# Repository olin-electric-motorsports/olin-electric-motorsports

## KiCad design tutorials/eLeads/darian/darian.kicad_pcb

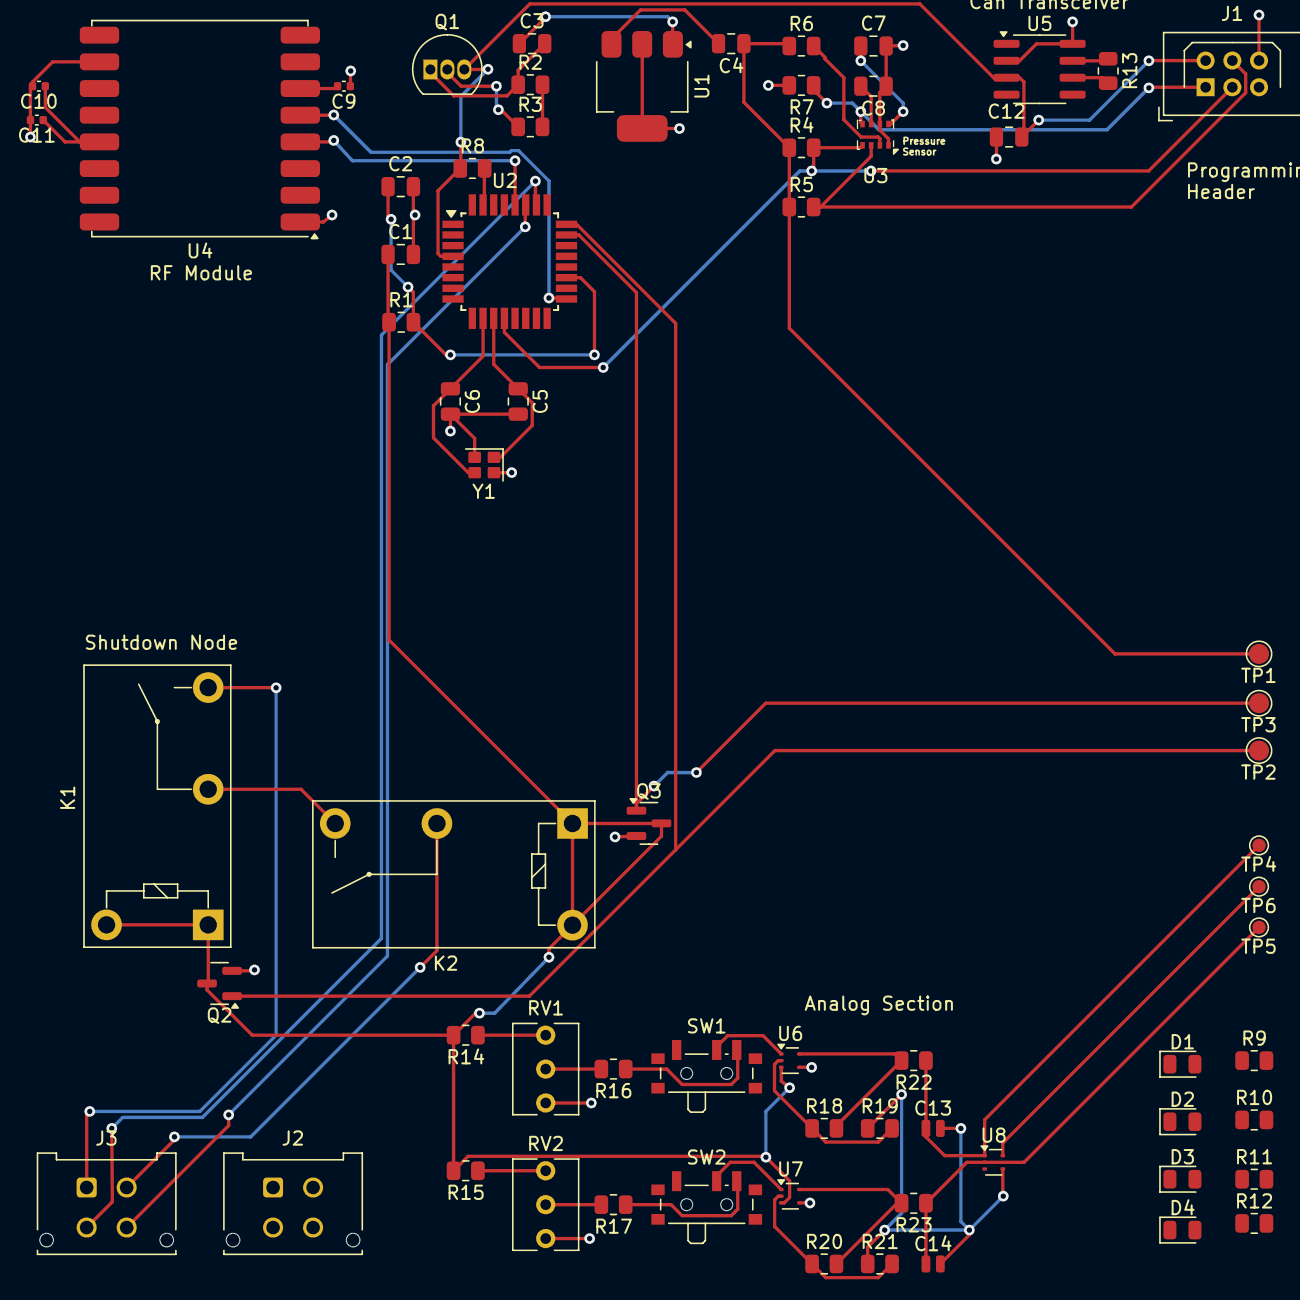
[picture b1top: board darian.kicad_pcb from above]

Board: 2 copper layers, 68 parts (0 on the bottom side), 51 nets.

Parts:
C1, C3, C4: C_1uF; C_0805_2012Metric
C2: C_100pF; C_0805_2012Metric
C5, C6: C_30pF; C_0805_2012Metric
C7, C8: C_100nF; C_0805_2012Metric
C9: C; C_0402_1005Metric
C10, C11: C_20pF; C_0402_1005Metric
C12: C_0.1uF; C_0805_2012Metric
C13, C14: C; C_0504_1310Metric
D1, D2, D3, D4: LED_0805; LED_0805_2012Metric
J1: CONN_02X03; Harwin_LTek-Male_2x03_P2.00mm_Vertical
J2, J3: MicroFit_RA_4; Molex_Micro-Fit_3.0_43045-0412_2x02_P3.00mm_Vertical
K1, K2: G5Q-1A4-DC5-5V; Relay_SPST_Omron-G5Q-1A
Q1: BC547; TO-92_Inline
Q2, Q3: SSM3K333R; SOT-23
R1: R_100; R_0805_2012Metric
R2, R3, R4, R5, R6, R7, R8: R_10K; R_0805_2012Metric
R9, R10, R11, R12, R14, R15, R16, R17, R18, R19, R20, R21, R22, R23: R_1K; R_0805_2012Metric
R13: R_120_DNP; R_0805_2012Metric
RV1, RV2: R_Potentiometer; Potentiometer_Vishay_T73XW_Horizontal
SW1, SW2: SW_SPDT; SW_SPDT_PCM12
TP1, TP2, TP3: TP; TestPoint_Pad_D1.5mm
TP4, TP5, TP6: TP_SMD; TestPoint_Pad_D1.0mm
U1: TC1262-33; SOT-223-3_TabPin2
U2: ATMEGA16M1; TQFP-32_7x7mm_P0.8mm
U3: BMP280; Bosch_LGA-8_2x2.5mm_P0.65mm_ClockwisePinNumbering
U4: RFM69HCW; HOPERF_RFM9XW_SMD
U5: TJA1042T; SOIC-8_3.9x4.9mm_P1.27mm
U6, U7, U8: ${SIM.PARAMS}; VSOF5
Y1: Crystal_12MHz; Crystal_SMD_SeikoEpson_FA128-4Pin_2.0x1.6mm

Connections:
+3.3V: C10.1, C11.1, R2.2, R3.2, U4.13 (3.3V)
+5V: C1.1, C12.2, J1.2, K1.1, K1.5, K2.1, K2.5, Q1.3 (E), Q2.3 (D), Q3.3 (D), R1.1, R8.1, R14.2, R15.2, U2.4 (VCC), U5.3 (VCC), U6.3 (V+), U7.3 (V+), U8.3 (V+)
/ANALOG_A: J3.3, U2.26 ((PCINT5/ADC6/INT2/ACMPN1/AMP2-)PB5)
/ANALOG_B: J3.4, U2.27 ((PCINT6/ADC7/PSCOUT1B)PB6)
/ANALOG_SS: Q2.1 (G), TP2.1 (TP), U2.24 ((PCINT4/AMP0+)PB4)
/Analog Section/ANALOG_OUT: TP6.1, U8.5
/CAN_RX: U2.7 ((PCINT11/T1/ICP1B/RXCAN)PC3), U5.4 (RXD)
/CAN_TX: U2.6 ((PCINT10/T0/TXCAN)PC2), U5.1 (TXD)
/MISO: J1.1, R7.1, U2.1 ((PCINT18/PSCIN2/OC1A/MISO_A)PD2), U2.8 ((PCINT0/MISO/PSCOUT2A)PB0), U3.5 (SDO), U4.2 (MISO)
/MOSI: J1.4, R5.2, U2.2 ((PCINT19/TXD/TXLIN/OC0A/~SS/MOSI_A)PD3), U2.9 ((PCINT1/MOSI/PSCOUT2B)PB1), U3.3 (SDI), U4.3 (MOSI)
/NSS: U2.17 ((PCINT12/ADC8/ACMPN3/AMP1-)PC4), U4.5 (NSS)
/Reset: R8.2, U2.31 ((PCINT24/OCD/~RESET)PE0)
/SCK: J1.3, R4.2, U2.12 ((PCINT20/ADC1/RXD/RXLIN/ICP1A/SCK_A)PD4), U2.28 ((PCINT7/ADC4/SCK/PSCOUT0B)PB7), U3.4 (SCK), U4.4 (SCK)
/SENSOR_SS: Q3.1 (G), TP3.1 (TP), U2.23 ((PCINT3/AMP0-)PB3)
/SHDN_IN: J3.1, K1.3
/SHDN_OUT: J3.2, K2.2
/Sensor: R6.2, U3.2 (CSB)
GND: C1.2, C2.2, C5.2, C6.2, C7.2, C8.1, C9.1, C10.2, C11.2, C12.1, C13.2, C14.2, J1.6, J2.2, Q2.2 (S), Q3.2 (S), R7.2, R9.1, R10.1, R11.1, R12.1, R19.1, R21.1, RV1.3, RV2.3, U1.2 (GND), U3.1 (GND), U3.7 (GND), U4.1 (GND), U4.10 (GND), U5.2 (GND), U5.8 (STB), U6.4 (V-), U7.4 (V-), U8.4 (V-), Y1.2, Y1.4
GND1: U2.5 (GND), U2.20 (AGND)
unnamed: D1.2 (A), R9.2
unnamed: D2.2 (A), R10.2
unnamed: D3.2 (A), R11.2
unnamed: D4.2 (A), R12.2
unnamed: K1.2, K2.3
unnamed: Q1.2 (B), R3.1
unnamed: C3.2, Q1.1 (C), R2.1
unnamed: R14.1, RV1.1
unnamed: R15.1, RV2.1
unnamed: R16.2, RV1.2
unnamed: R17.2, RV2.2
unnamed: R18.2, R22.2, U6.5
unnamed: R20.2, R23.2, U7.5
unnamed: SW1.2 (B), U6.1 (+)
unnamed: R16.1, SW1.3 (C)
unnamed: SW2.2 (B), U7.1 (+)
unnamed: R17.1, SW2.3 (C)
unnamed: C4.1, R4.1, R5.1, R6.1, TP1.1 (TP)
unnamed: C3.1, U1.1 (VI)
unnamed: C4.2, U1.3 (VO)
unnamed: C6.1, U2.10 ((PCINT25/OC0B/XTAL1)PE1), Y1.3
unnamed: C5.1, U2.11 ((PCINT26/ADC0/XTAL2)PE2), Y1.1
unnamed: C2.1, R1.2, U2.19 (AVCC)
unnamed: C7.1, U3.8 (VDD)
unnamed: C8.2, U3.6 (VDDIO)
unnamed: C9.2, U4.6 (RESET)
unnamed: R13.1, U5.7 (CANH)
unnamed: R13.2, U5.6 (CANL)
unnamed: R18.1, R19.2, U6.2 (-)
unnamed: R20.1, R21.2, U7.2 (-)
unnamed: C13.1, R22.1, TP4.1, U8.1 (+)
unnamed: C14.1, R23.1, TP5.1, U8.2 (-)

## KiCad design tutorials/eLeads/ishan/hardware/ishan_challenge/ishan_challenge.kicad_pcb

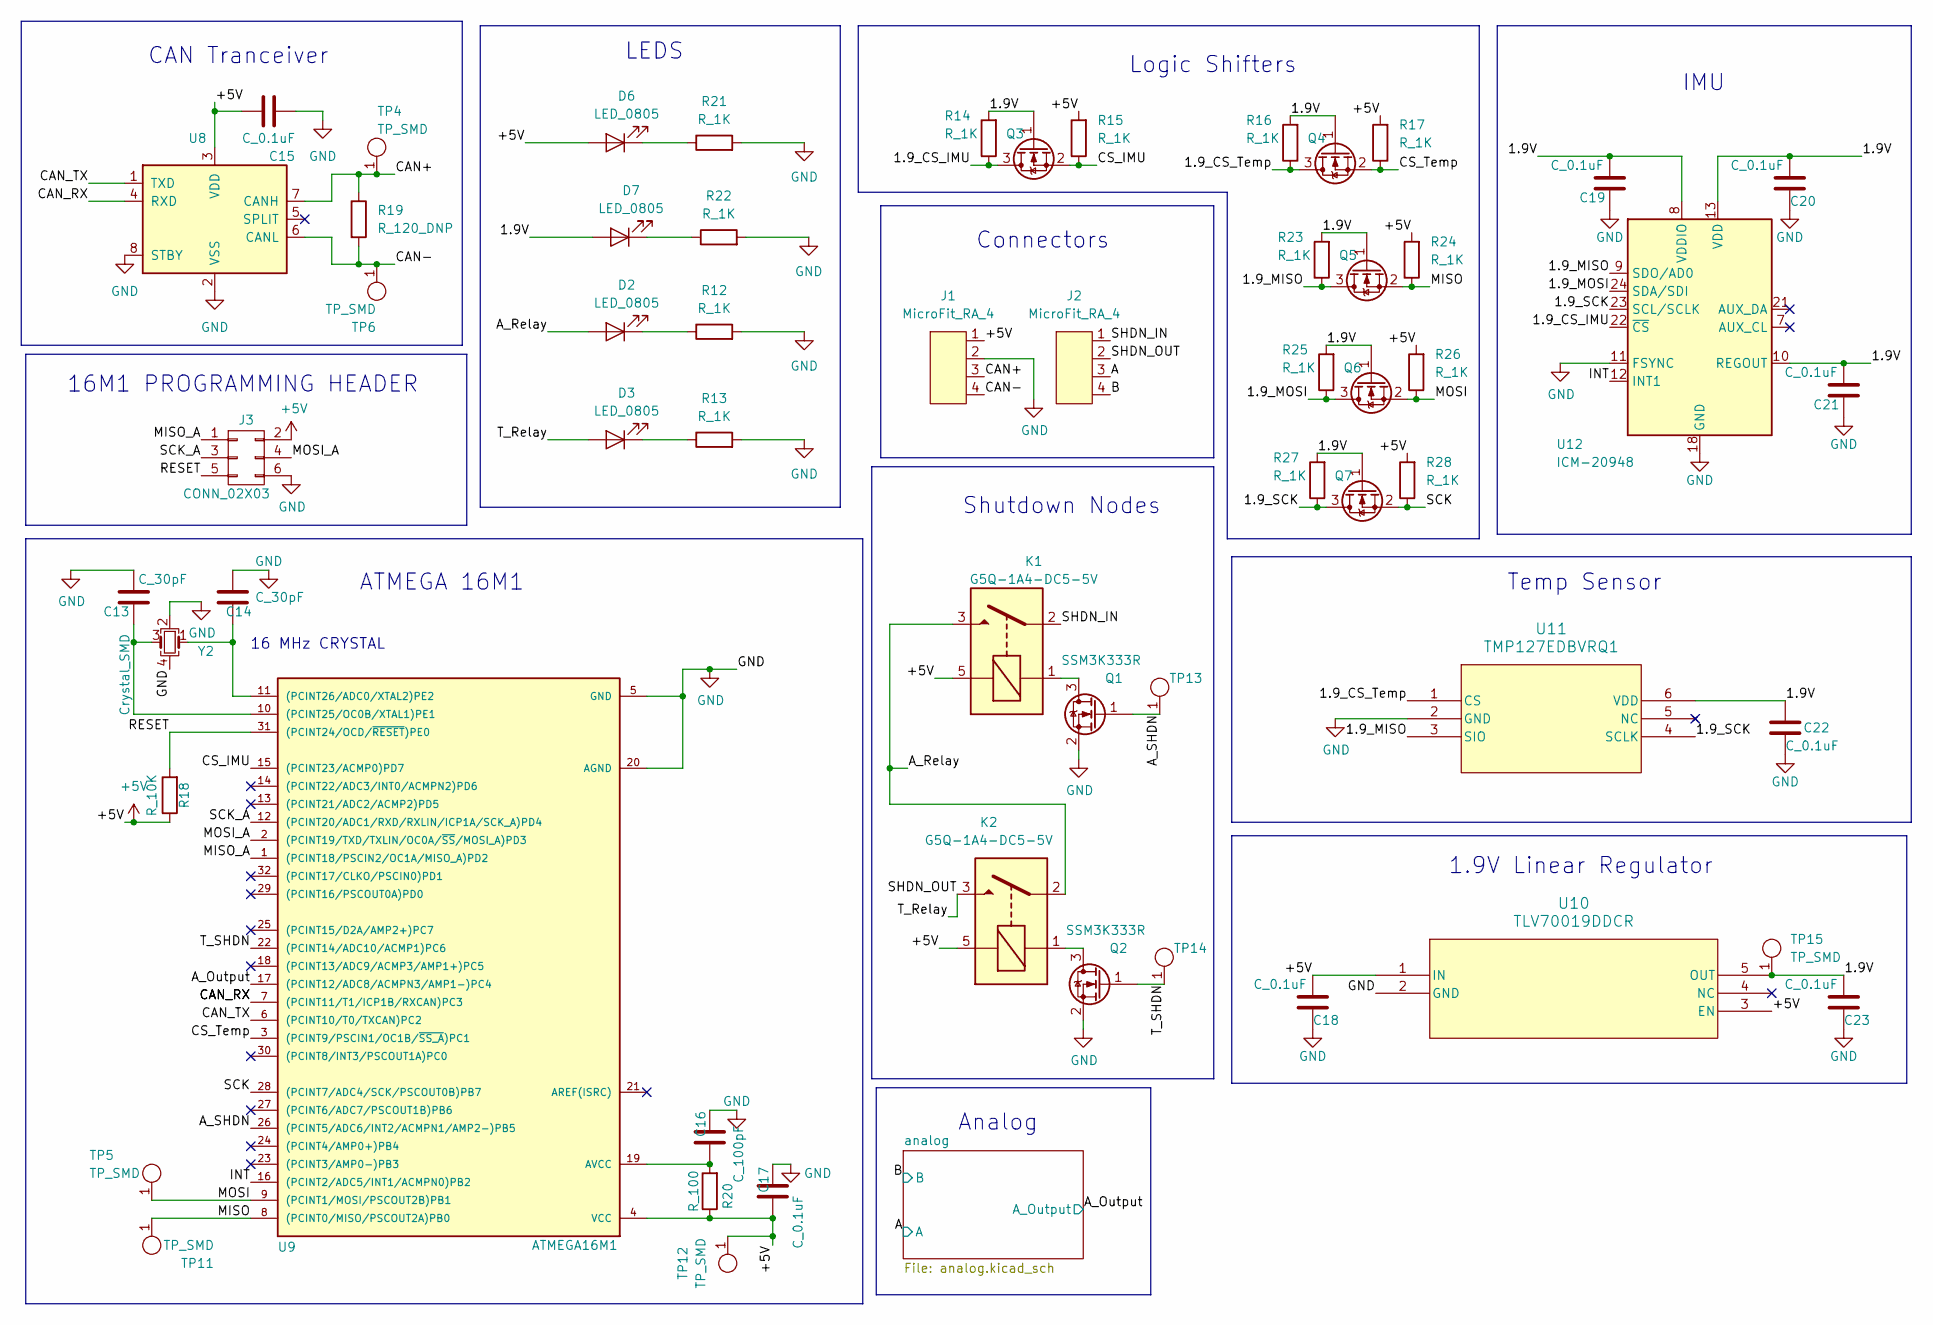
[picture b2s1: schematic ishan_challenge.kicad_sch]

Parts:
C13, C14: C_30pF; C_0603; MPN 1276-1130-1-ND
C15, C17: C_0.1uF; C_0603; MPN 478-3352-1-ND
C16: C_100pF; C_0603; MPN 732-7852-1-ND
C18, C19, C20, C21, C22, C23: C_0.1uF; C_0603; MPN 1276-1130-1-ND
D2, D3, D6, D7: LED_0805; LED_0805_OEM; MPN 475-1410-1-ND
J1, J2: MicroFit_RA_4
J3: CONN_02X03; Pin_Header_Straight_2x03; MPN 609-3234-ND
K1, K2: G5Q-1A4-DC5-5V; Relay_SPST_OMRON-G5Q-1A4_OEM; MPN Z3632-ND
Q1, Q2, Q3, Q4, Q5, Q6, Q7: SSM3K333R; SOT-23F; MPN SSM3K333RLFCT-ND
R12, R13, R14, R15, R16, R17, R21, R22, R23, R24, R25, R26, R27, R28: R_1K; R_0603; MPN RNCP0805FTD1K00CT-ND
R18: R_10K; R_0603; MPN CRS0805-FX-1002ELFCT-ND
R19: R_120_DNP; R_0603; MPN 667-ERJ-6ENF1200V
R20: R_100; R_0603; MPN RNCP0805FTD100RCT-ND
TP4, TP5, TP6, TP11, TP12, TP13, TP14, TP15: TP_SMD; Test_Point_SMD; MPN 5019
U8: MCP2561-E_SN; SOIC-8_3.9x4.9mm_Pitch1.27mm_OEM; MPN MCP2561-E/SN-ND
U9: ATMEGA16M1; TQFP-32_7x7mm_Pitch0.8mm; MPN ATMEGA16M1-AU-ND
U10: TLV70019DDCR
U11: TMP127EDBVRQ1
U12: ICM-20948; InvenSense_QFN-24_3x3mm_P0.4mm
Y2: Crystal_SMD; Crystal_SMD_FA238; MPN 887-1125-1-ND

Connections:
+5V: C15.1, C17.1, C18.2, D6.2 (A), J1.1, J3.2, K1.5, K2.5, R15.2, R17.2, R18.1, R20.1, R24.2, R26.2, R28.2, TP12.1, U8.3 (VDD), U9.4 (VCC), U10.1 (IN), U10.3 (EN); also elsewhere on the board
/1.9V: C19.2, C20.2, C21.2, C22.2, C23.2, D7.2 (A), Q3.1 (G), Q4.1 (G), Q5.1 (G), Q6.1 (G), Q7.1 (G), R14.2, R16.2, R23.2, R25.2, R27.2, TP15.1, U10.5 (OUT), U11.6 (VDD), U12.8 (VDDIO), U12.10 (REGOUT), U12.13 (VDD)
/1.9_CS_IMU: Q3.3 (D), R14.1, U12.22 (~CS)
/1.9_CS_Temp: Q4.3 (D), R16.1, U11.1 (CS)
/1.9_MISO: Q5.3 (D), R23.1, U11.3 (SIO), U12.9 (SDO/AD0)
/1.9_MOSI: Q6.3 (D), R25.1, U12.24 (SDA/SDI)
/1.9_SCK: Q7.3 (D), R27.1, U11.4 (SCLK), U12.23 (SCL/SCLK)
/A: J2.3; also elsewhere on the board
/A_Output: U9.17 ((PCINT12/ADC8/ACMPN3/AMP1-)PC4); also elsewhere on the board
/A_Relay: D2.2 (A), K1.3, K2.2
/A_SHDN: Q1.1 (G), TP13.1, U9.26 ((PCINT5/ADC6/INT2/ACMPN1/AMP2-)PB5)
/B: J2.4; also elsewhere on the board
/CAN+: J1.3, R19.1, TP4.1, U8.7 (CANH)
/CAN-: J1.4, R19.2, TP6.1, U8.6 (CANL)
/CAN_RX: U8.4 (RXD), U9.7 ((PCINT11/T1/ICP1B/RXCAN)PC3)
/CAN_TX: U8.1 (TXD), U9.6 ((PCINT10/T0/TXCAN)PC2)
/CS_IMU: Q3.2 (S), R15.1, U9.15 ((PCINT23/ACMP0)PD7)
/CS_Temp: Q4.2 (S), R17.1, U9.3 ((PCINT9/PSCIN1/OC1B/~SS_A)PC1)
/INT: U9.16 ((PCINT2/ADC5/INT1/ACMPN0)PB2), U12.12 (INT1)
/MISO: Q5.2 (S), R24.1, TP11.1, U9.8 ((PCINT0/MISO/PSCOUT2A)PB0)
/MISO_A: J3.1, U9.1 ((PCINT18/PSCIN2/OC1A/MISO_A)PD2)
/MOSI: Q6.2 (S), R26.1, TP5.1, U9.9 ((PCINT1/MOSI/PSCOUT2B)PB1)
/MOSI_A: J3.4, U9.2 ((PCINT19/TXD/TXLIN/OC0A/~SS/MOSI_A)PD3)
/RESET: J3.5, R18.2, U9.31 ((PCINT24/OCD/~RESET)PE0)
/SCK: Q7.2 (S), R28.1, U9.28 ((PCINT7/ADC4/SCK/PSCOUT0B)PB7)
/SCK_A: J3.3, U9.12 ((PCINT20/ADC1/RXD/RXLIN/ICP1A/SCK_A)PD4)
/SHDN_IN: J2.1, K1.2
/SHDN_OUT: D3.2 (A), J2.2, K2.3
/T_SHDN: Q2.1 (G), TP14.1, U9.22 ((PCINT14/ADC10/ACMP1)PC6)
unnamed: D2.1 (K), R12.1
unnamed: D3.1 (K), R13.1
unnamed: D6.1 (K), R21.1
unnamed: D7.1 (K), R22.1
unnamed: K1.1, Q1.3 (D)
unnamed: K2.1, Q2.3 (D)
unnamed: C13.1, U9.10 ((PCINT25/OC0B/XTAL1)PE1), Y2.3
unnamed: C14.1, U9.11 ((PCINT26/ADC0/XTAL2)PE2), Y2.1
unnamed: C16.1, R20.2, U9.19 (AVCC)

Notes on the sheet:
Logic Shifters
LEDS
Connectors
Analog
Shutdown Nodes
Temp Sensor
IMU
16M1 PROGRAMMING HEADER
16 MHz CRYSTAL
1.9V Linear Regulator
CAN Tranceiver
ATMEGA 16M1

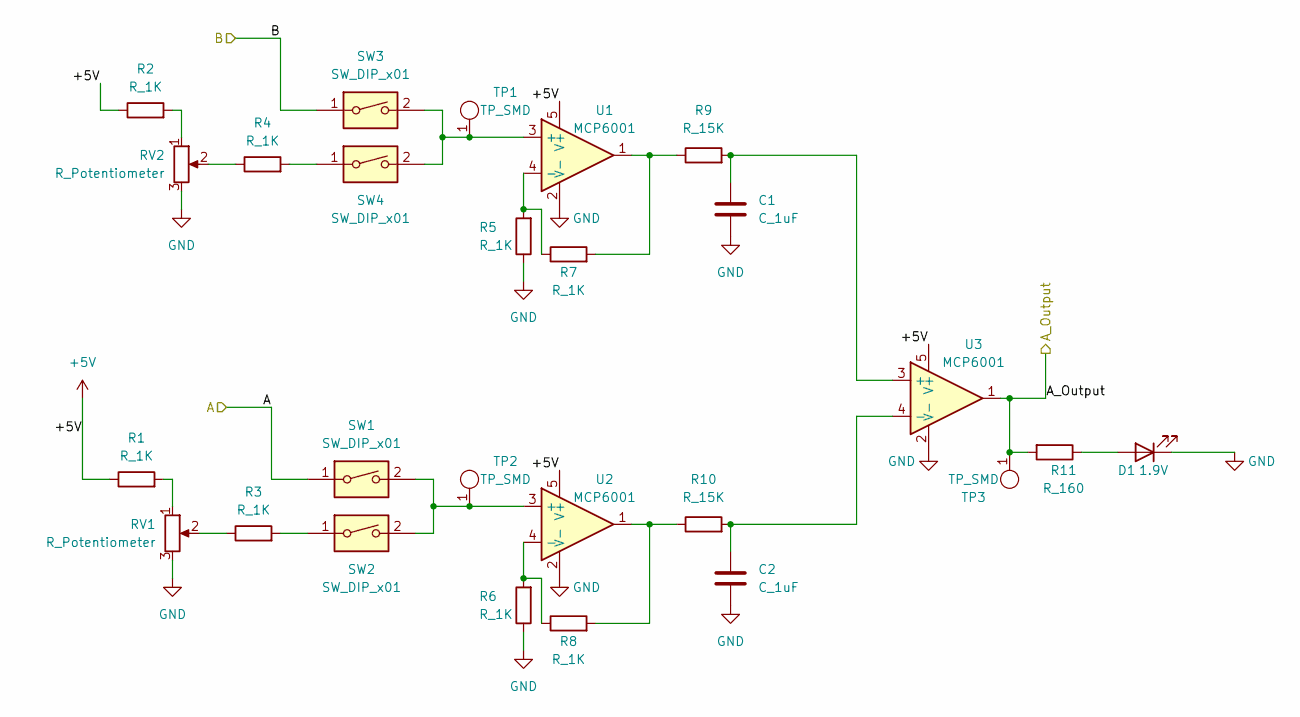
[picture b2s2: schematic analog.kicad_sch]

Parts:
C1, C2: C_1uF; C_0603; MPN 1276-6470-1-ND
D1: 1.9V; LED_0805_OEM; MPN B1701TW--20P000314U1930
R1, R2, R3, R4, R5, R6, R7, R8: R_1K; R_0603; MPN RNCP0805FTD1K00CT-ND
R9, R10: R_15K; R_0603; MPN RNCP0805FTD1K00CT-ND
R11: R_160; R_0603; MPN 311-4.7KARCT-ND
RV1, RV2: R_Potentiometer; Potentiometer_Trimmer_Bourns_TCC3
SW1, SW2, SW3, SW4: SW_DIP_x01; SW_DIP_SPSTx01_Slide_9.78x4.72mm_W8.61mm_P2.54mm
TP1, TP2, TP3: TP_SMD; Test_Point_SMD; MPN 5019
U1, U2, U3: MCP6001; SOT-23-5_OEM; MPN MCP6001T-I/OTCT-ND

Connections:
+5V: R1.1, R2.1, U1.5 (V+), U2.5 (V+), U3.5 (V+); also elsewhere on the board
/A: SW1.1; also elsewhere on the board
/A_Output: R11.2, TP3.1, U3.1; also elsewhere on the board
/B: SW3.1; also elsewhere on the board
unnamed: D1.2 (A), R11.1
unnamed: R1.2, RV1.1
unnamed: R2.2, RV2.1
unnamed: R3.1, RV1.2
unnamed: R3.2, SW2.1
unnamed: R4.1, RV2.2
unnamed: R4.2, SW4.1
unnamed: R7.2, R9.1, U1.1
unnamed: R8.2, R10.1, U2.1
unnamed: SW3.2, SW4.2, TP1.1, U1.3 (+)
unnamed: R5.2, R7.1, U1.4 (-)
unnamed: SW1.2, SW2.2, TP2.1, U2.3 (+)
unnamed: R6.2, R8.1, U2.4 (-)
unnamed: C1.1, R9.2, U3.3 (+)
unnamed: C2.1, R10.2, U3.4 (-)

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
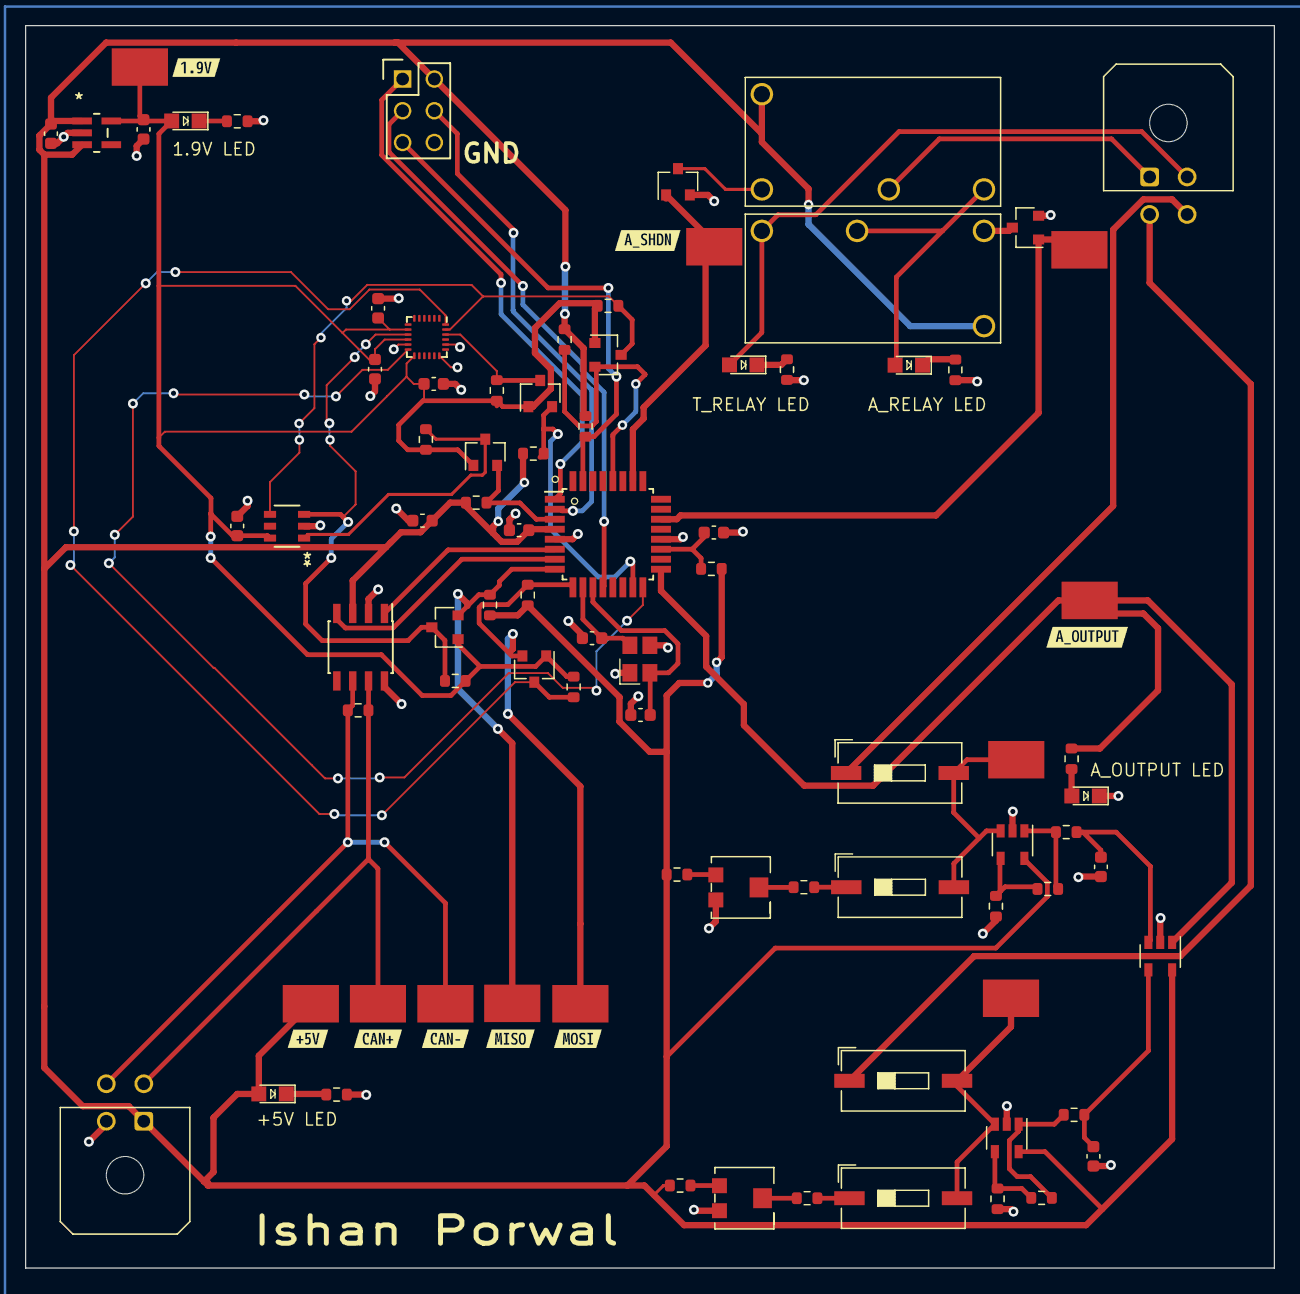
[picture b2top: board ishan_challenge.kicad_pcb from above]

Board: 2 copper layers, 99.9 x 99.4 mm, 92 parts (0 on the bottom side), 54 nets.

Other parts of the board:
kibuzzard-66BA7B45: G***; kibuzzard-66BA7B45
kibuzzard-66BA78DD: G***; kibuzzard-66BA78DD
kibuzzard-66BA78FC: G***; kibuzzard-66BA78FC
kibuzzard-66BA794C: G***; kibuzzard-66BA794C
kibuzzard-66BA7730: G***; kibuzzard-66BA7730
kibuzzard-66BA7778: G***; kibuzzard-66BA7778
kibuzzard-66BA7799: G***; kibuzzard-66BA7799
kibuzzard-66BA7937: G***; kibuzzard-66BA7937

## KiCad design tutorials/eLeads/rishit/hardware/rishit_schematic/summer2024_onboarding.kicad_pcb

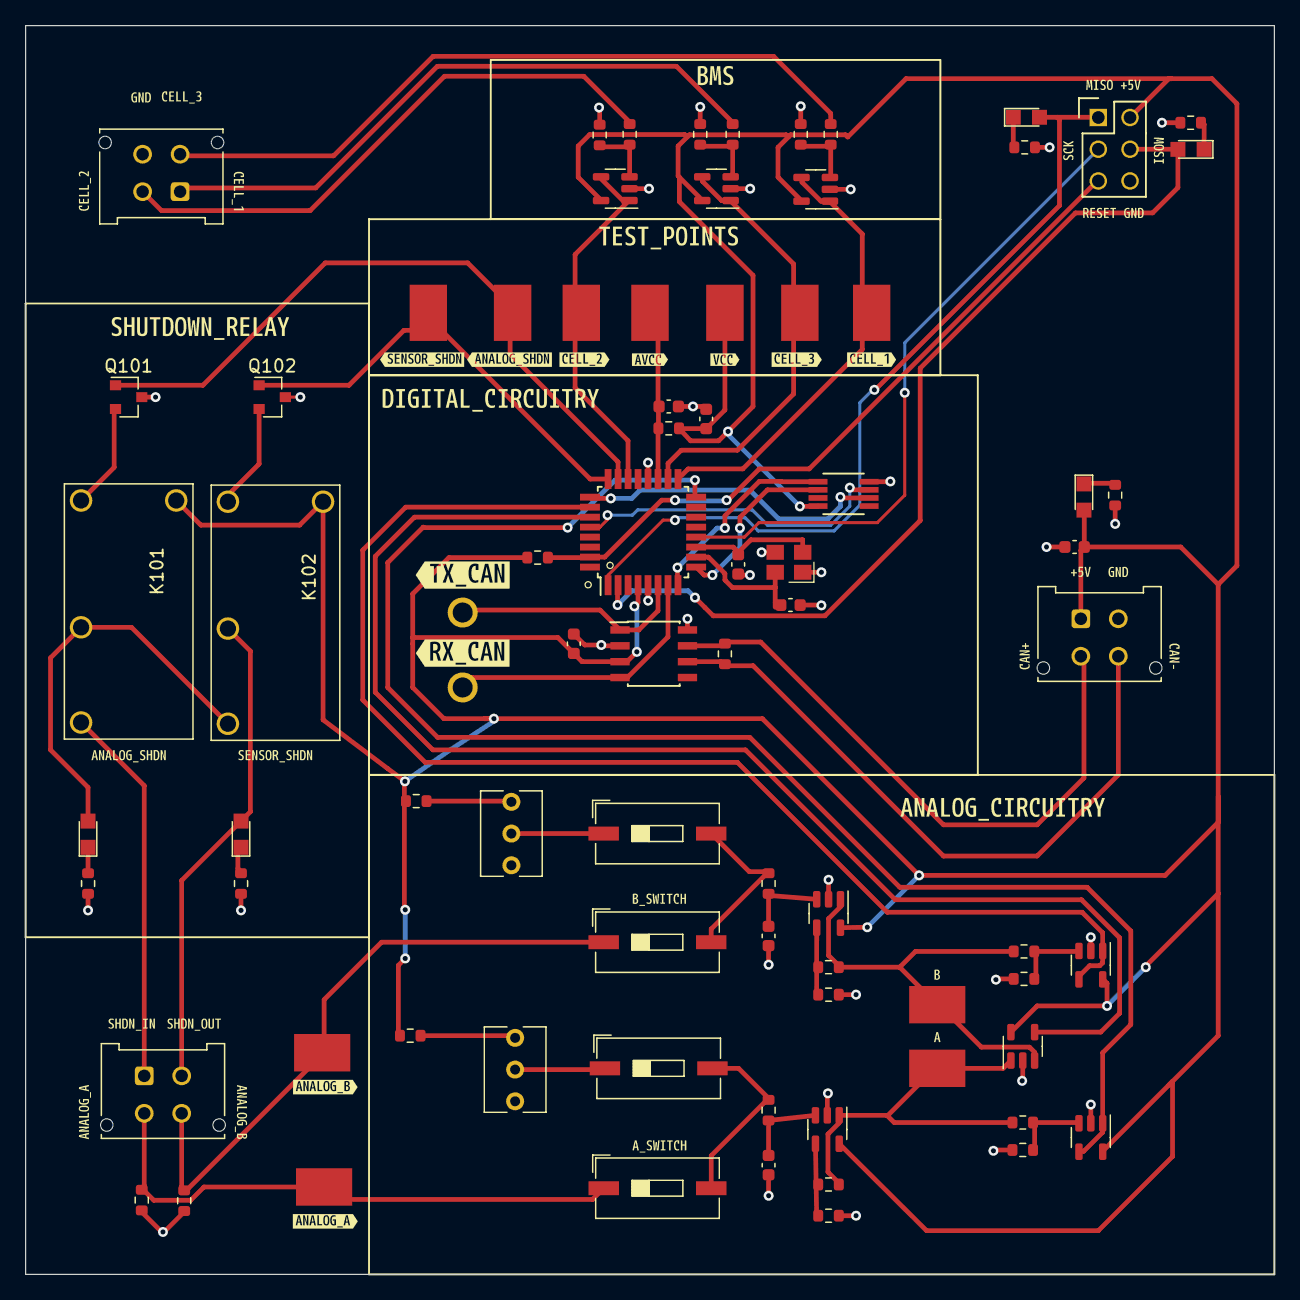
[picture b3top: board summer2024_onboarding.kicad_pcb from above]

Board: 2 copper layers, 100.0 x 100.0 mm, 120 parts (0 on the bottom side), 57 nets.

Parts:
C101, C105, C108: C_0.1uF; C_0603
C102: C_100pF; C_0603
C103, C104: C_30pF; C_0603
C106, C107: C_10uF; C_0603
D101, D104, D105: 5V_LED; CHIPLED_0805
D102: MISO_PROG_LED; CHIPLED_0805
D103: MOSI_PROG_LED; CHIPLED_0805
J101: Conn_02x03_Odd_Even; Pin_Header_Straight_2x03
J102, J103, J104: MicroFit_VT_4
K101, K102: G5Q-1A4-DC5-5V; Relay_SPST_OMRON-G5Q-1A4_OEM
Q101, Q102: SSM3K333R; SOT-23F
R101: R_100; R_0603
R102: R_10K; R_0603
R103: R_120_DNP; R_0603
R104, R105, R106, R107, R108, R109, R110, R111, R112, R113, R114, R115, R116, R117, R118, R119, R120, R121, R122, R123, R124, R127, R128: R_1K; R_0603
R125, R126: R_100K; R_0603
RV101, RV102: R_Potentiometer; Potentiometer_Vishay_T73XW_Horizontal
SW101, SW102, SW103, SW104: SW_DIP_x01; SW_DIP_SPSTx01_Slide_9.78x4.72mm_W8.61mm_P2.54mm
TP101, TP102, TP104, TP107, TP108, TP109, TP110, TP111, TP112, TP113, TP115: TP_SMD; Test_Point_SMD
TP105, TP106: TP; tp_1.6mm
U101: ATMEGA16M1; TQFP-32_7x7mm_Pitch0.8mm
U102: MCP2561-E_SN; SOIC-8_3.9x4.9mm_Pitch1.27mm_OEM
U103: TC72-3.3MUATR; MSOP8_MC_MCH
U104, U105, U106, U107, U109, U110, U111: MCP6001; SOT-23-5
U108: LM397; SOT-23-5
Y101: Crystal_16MHz_18pF; Crystal_SMD_FA238
kibuzzard-66BE6AB2: G***; kibuzzard-66BE6AB2
kibuzzard-66BE6ACE: G***; kibuzzard-66BE6ACE
kibuzzard-66BE71B0: G***; kibuzzard-66BE71B0
kibuzzard-66BE71DF: G***; kibuzzard-66BE71DF
kibuzzard-66BE71E9: G***; kibuzzard-66BE71E9
kibuzzard-66BE71F1: G***; kibuzzard-66BE71F1
kibuzzard-66BE71FF: G***; kibuzzard-66BE71FF
kibuzzard-66BE72A1: G***; kibuzzard-66BE72A1
kibuzzard-66BE72AD: G***; kibuzzard-66BE72AD
kibuzzard-66BE72B5: G***; kibuzzard-66BE72B5
kibuzzard-66BE72C2: G***; kibuzzard-66BE72C2
kibuzzard-66BE72DA: G***; kibuzzard-66BE72DA
kibuzzard-66BE72F1: G***; kibuzzard-66BE72F1
kibuzzard-66BE686E: G***; kibuzzard-66BE686E
kibuzzard-66BE690E: G***; kibuzzard-66BE690E
kibuzzard-66BE691A: G***; kibuzzard-66BE691A
kibuzzard-66BE692C: G***; kibuzzard-66BE692C
kibuzzard-66BE702D: G***; kibuzzard-66BE702D
kibuzzard-66BE725D: G***; kibuzzard-66BE725D
kibuzzard-66BE726A: G***; kibuzzard-66BE726A
kibuzzard-66BE736C: G***; kibuzzard-66BE736C
kibuzzard-66BE6860: G***; kibuzzard-66BE6860
kibuzzard-66BE6937: G***; kibuzzard-66BE6937
kibuzzard-66BE7023: G***; kibuzzard-66BE7023
kibuzzard-66BE7118: G***; kibuzzard-66BE7118
kibuzzard-66BE7123: G***; kibuzzard-66BE7123
kibuzzard-66BE7184: G***; kibuzzard-66BE7184
kibuzzard-66BE7235: G***; kibuzzard-66BE7235
kibuzzard-66BE7274: G***; kibuzzard-66BE7274
kibuzzard-66BF40E2: G***; kibuzzard-66BF40E2
kibuzzard-66BF42D8: G***; kibuzzard-66BF42D8
kibuzzard-66BF42E1: G***; kibuzzard-66BF42E1
kibuzzard-66BF415D: G***; kibuzzard-66BF415D
kibuzzard-66BF4127: G***; kibuzzard-66BF4127
kibuzzard-66BF4146: G***; kibuzzard-66BF4146
kibuzzard-66BF4157: G***; kibuzzard-66BF4157
kibuzzard-66BF4165: G***; kibuzzard-66BF4165
kibuzzard-66BF4194: G***; kibuzzard-66BF4194
kibuzzard-66BF4328: G***; kibuzzard-66BF4328
kibuzzard-66BF4330: G***; kibuzzard-66BF4330

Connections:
+5V: C101.1, C105.1, C108.2, D101.2 (A), J101.2, J102.1, K101.5, K102.5, R101.1, R102.2, R107.1, R108.1, TP102.1, U101.4 (VCC), U102.3 (VDD), U103.8, U104.5 (V+), U105.5 (V+), U106.5 (V+), U107.5 (V+), U108.5 (V+), U109.5 (V+), U110.5 (V+), U111.5 (V+)
/ANALOG_A: J103.3, R126.1, SW103.1, TP115.1
/ANALOG_B: J103.4, R125.1, SW101.1, TP108.1
/ANALOG_OUT: U101.27 ((PCINT6/ADC7/PSCOUT1B)PB6), U108.4
/ANALOG_SHDN: Q101.1 (G), TP104.1, U101.23 ((PCINT3/AMP0-)PB3)
/ANALOG_VOLTAGE_A: U101.16 ((PCINT2/ADC5/INT1/ACMPN0)PB2), U106.1, U106.4 (-)
/ANALOG_VOLTAGE_B: U101.26 ((PCINT5/ADC6/INT2/ACMPN1/AMP2-)PB5), U107.1, U107.4 (-)
/CAN+: J102.3, R103.1, U102.7 (CANH)
/CAN-: J102.4, R103.2, U102.6 (CANL)
/CE: U101.25 ((PCINT15/D2A/AMP2+)PC7), U103.2
/CELL_1: J104.1, R119.1
/CELL_2: J104.2, R123.1
/CELL_3: J104.3, R120.1
/MISO: U101.8 ((PCINT0/MISO/PSCOUT2A)PB0), U103.5
/MISO_A: D102.2 (A), J101.1, U101.1 ((PCINT18/PSCIN2/OC1A/MISO_A)PD2)
/MOSI: U101.9 ((PCINT1/MOSI/PSCOUT2B)PB1), U103.6
/MOSI_A: D103.2 (A), J101.4, U101.2 ((PCINT19/TXD/TXLIN/OC0A/~SS/MOSI_A)PD3)
/RESET: J101.5, R102.1, U101.31 ((PCINT24/OCD/~RESET)PE0)
/RXCAN: TP106.1 (TP), U101.7 ((PCINT11/T1/ICP1B/RXCAN)PC3), U102.4 (RXD)
/SCK: U101.28 ((PCINT7/ADC4/SCK/PSCOUT0B)PB7), U103.3
/SCK_A: J101.3, U101.12 ((PCINT20/ADC1/RXD/RXLIN/ICP1A/SCK_A)PD4)
/SENSOR_SHDN: Q102.1 (G), TP107.1, U101.24 ((PCINT4/AMP0+)PB4)
/TXCAN: TP105.1 (TP), U101.6 ((PCINT10/T0/TXCAN)PC2), U102.1 (TXD)
/VOLTAGE_CELL_1: TP110.1, U101.17 ((PCINT12/ADC8/ACMPN3/AMP1-)PC4), U110.1, U110.4 (-)
/VOLTAGE_CELL_2: TP112.1, U101.22 ((PCINT14/ADC10/ACMP1)PC6), U111.1, U111.4 (-)
/VOLTAGE_CELL_3: TP111.1, U101.18 ((PCINT13/ADC9/ACMP3/AMP1+)PC5), U109.1, U109.4 (-)
GND: C101.2, C102.2, C103.2, C104.2, C105.2, C106.2, C107.2, C108.1, J101.6, J102.2, J104.4, Q101.3 (D), Q102.3 (D), R104.2, R105.2, R106.2, R112.2, R114.2, R117.2, R118.2, R121.2, R122.2, R124.2, R125.2, R126.2, R127.2, R128.2, RV101.3, RV102.3, U101.5 (GND), U101.20 (AGND), U102.2 (VSS), U102.8 (STBY), U103.4, U104.2 (V-), U105.2 (V-), U106.2 (V-), U107.2 (V-), U108.2 (V-), U109.2 (V-), U110.2 (V-), U111.2 (V-), Y101.2, Y101.4
unnamed: D101.1 (K), R104.1
unnamed: D102.1 (K), R105.1
unnamed: D103.1 (K), R106.1
unnamed: D104.2 (A), K101.2, K102.3
unnamed: D104.1 (K), R127.1
unnamed: D105.1 (K), R128.1
unnamed: K101.1, Q101.2 (S)
unnamed: K102.1, Q102.2 (S)
unnamed: R107.2, RV101.1
unnamed: R108.2, RV102.1
unnamed: R109.1, SW101.2, SW102.2
unnamed: R110.1, SW103.2, SW104.2
unnamed: RV101.2, SW104.1
unnamed: RV102.2, SW102.1
unnamed: C104.1, U101.10 ((PCINT25/OC0B/XTAL1)PE1), Y101.3
unnamed: C103.1, U101.11 ((PCINT26/ADC0/XTAL2)PE2), Y101.1
unnamed: C102.1, R101.2, TP101.1, U101.19 (AVCC)
unnamed: C106.1, R109.2, U104.3 (+)
unnamed: R111.2, R112.1, U104.4 (-)
unnamed: C107.1, R110.2, U105.3 (+)
unnamed: R113.2, R114.1, U105.4 (-)
unnamed: R115.2, R117.1, U106.3 (+)
unnamed: R116.2, R118.1, U107.3 (+)
unnamed: R111.1, R116.1, TP109.1, U104.1, U108.3 (+)
unnamed: R113.1, R115.1, TP113.1, U105.1, U108.1 (-)
unnamed: R119.2, R121.1, U109.3 (+)
unnamed: R120.2, R122.1, U110.3 (+)
unnamed: R123.2, R124.1, U111.3 (+)
SHDN_IN: J103.1, K101.3
SHDN_OUT: D105.2 (A), J103.2, K102.2

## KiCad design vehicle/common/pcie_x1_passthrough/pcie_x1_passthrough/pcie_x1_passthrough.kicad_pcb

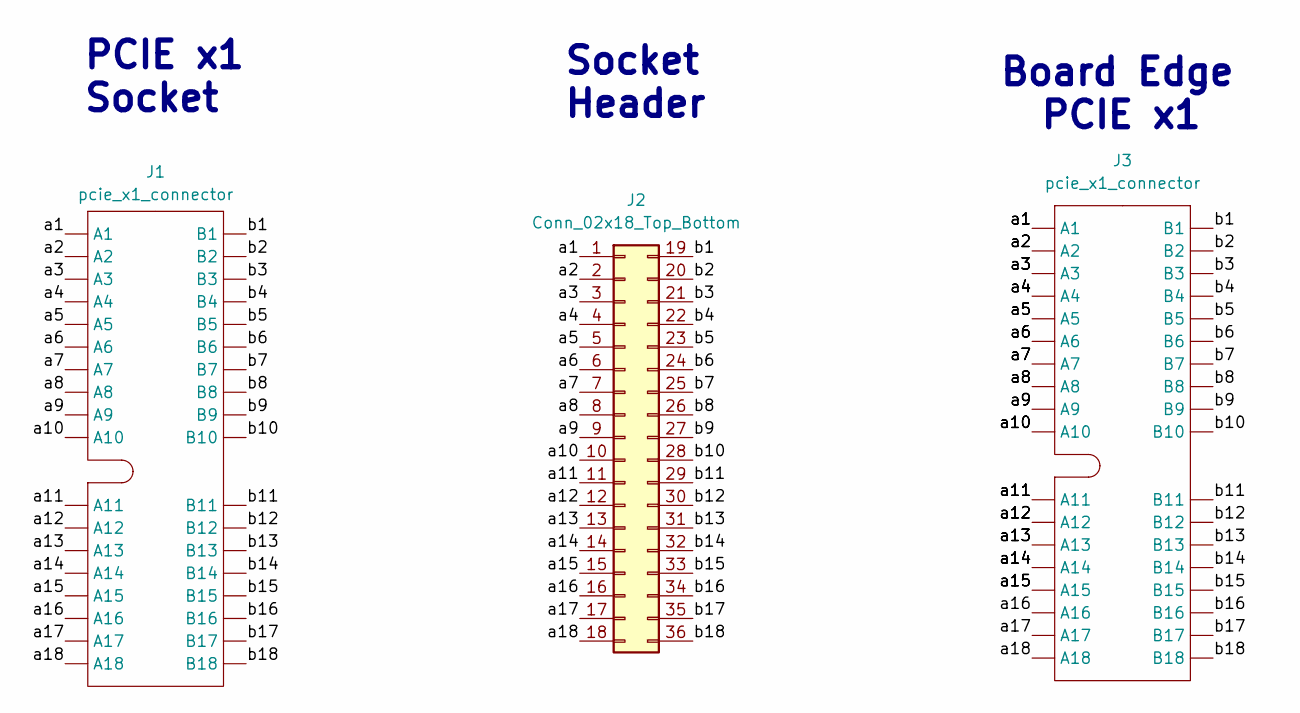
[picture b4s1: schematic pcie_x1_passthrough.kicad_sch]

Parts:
J1: pcie_x1_connector; pcie_x1_socket
J2: Conn_02x18_Top_Bottom; PinSocket_2x18_P2.54mm_Vertical
J3: pcie_x1_connector; BUS_PCIexpress_x1

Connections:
/a1: J1.A1, J2.1, J3.A1
/a2: J1.A2, J2.2, J3.A2
/a3: J1.A3, J2.3, J3.A3
/a4: J1.A4, J2.4, J3.A4
/a5: J1.A5, J2.5, J3.A5
/a6: J1.A6, J2.6, J3.A6
/a7: J1.A7, J2.7, J3.A7
/a8: J1.A8, J2.8, J3.A8
/a9: J1.A9, J2.9, J3.A9
/a10: J1.A10, J2.10, J3.A10
/a11: J1.A11, J2.11, J3.A11
/a12: J1.A12, J2.12, J3.A12
/a13: J1.A13, J2.13, J3.A13
/a14: J1.A14, J2.14, J3.A14
/a15: J1.A15, J2.15, J3.A15
/a16: J1.A16, J2.16, J3.A16
/a17: J1.A17, J2.17, J3.A17
/a18: J1.A18, J2.18, J3.A18
/b1: J1.B1, J2.19, J3.B1
/b2: J1.B2, J2.20, J3.B2
/b3: J1.B3, J2.21, J3.B3
/b4: J1.B4, J2.22, J3.B4
/b5: J1.B5, J2.23, J3.B5
/b6: J1.B6, J2.24, J3.B6
/b7: J1.B7, J2.25, J3.B7
/b8: J1.B8, J2.26, J3.B8
/b9: J1.B9, J2.27, J3.B9
/b10: J1.B10, J2.28, J3.B10
/b11: J1.B11, J2.29, J3.B11
/b12: J1.B12, J2.30, J3.B12
/b13: J1.B13, J2.31, J3.B13
/b14: J1.B14, J2.32, J3.B14
/b15: J1.B15, J2.33, J3.B15
/b16: J1.B16, J2.34, J3.B16
/b17: J1.B17, J2.35, J3.B17
/b18: J1.B18, J2.36, J3.B18

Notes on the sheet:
Socket Header
Board Edge PCIE x1
PCIE x1 Socket

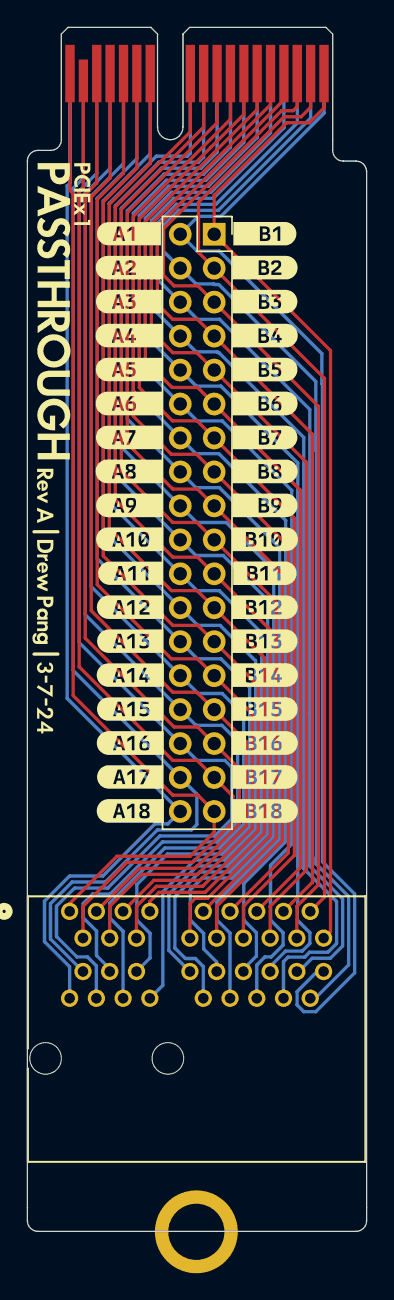
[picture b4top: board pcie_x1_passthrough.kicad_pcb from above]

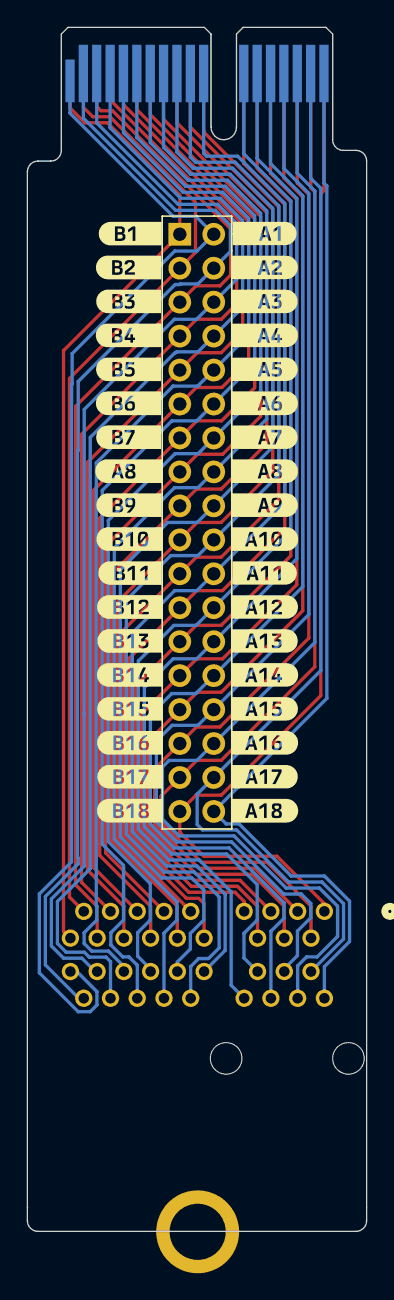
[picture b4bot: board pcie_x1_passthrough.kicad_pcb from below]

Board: 2 copper layers, 25.4 x 90.1 mm, 79 parts (37 on the bottom side), 36 nets.

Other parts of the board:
J2#2: Conn_02x18_Top_Bottom; PinSocket_2x18_P2.54mm_Vertical
kibuzzard-65E95D19: G***; kibuzzard-65E95D19
kibuzzard-65E95DA8: G***; kibuzzard-65E95DA8
kibuzzard-65E95DDF, kibuzzard-65E95DDF#2: G***; kibuzzard-65E95DDF
kibuzzard-65E95DE4: G***; kibuzzard-65E95DE4
kibuzzard-65E95DEB: G***; kibuzzard-65E95DEB
kibuzzard-65E95DEF: G***; kibuzzard-65E95DEF
kibuzzard-65E95DF3: G***; kibuzzard-65E95DF3
kibuzzard-65E95DF8: G***; kibuzzard-65E95DF8
kibuzzard-65E95DFB: G***; kibuzzard-65E95DFB
kibuzzard-65E95E04: G***; kibuzzard-65E95E04
kibuzzard-65E95E8F: G***; kibuzzard-65E95E8F
kibuzzard-65E95E9B: G***; kibuzzard-65E95E9B
kibuzzard-65E95E9E: G***; kibuzzard-65E95E9E
kibuzzard-65E95E93: G***; kibuzzard-65E95E93
kibuzzard-65E95E97: G***; kibuzzard-65E95E97
kibuzzard-65E95EA2: G***; kibuzzard-65E95EA2
kibuzzard-65E95EA8: G***; kibuzzard-65E95EA8
kibuzzard-65E95EAD: G***; kibuzzard-65E95EAD
kibuzzard-65E95F03: G***; kibuzzard-65E95F03
kibuzzard-65E960EE: G***; kibuzzard-65E960EE
kibuzzard-65E962FB: G***; kibuzzard-65E962FB
kibuzzard-65E962FE: G***; kibuzzard-65E962FE
kibuzzard-65E963A3: G***; kibuzzard-65E963A3
kibuzzard-65E963A9: G***; kibuzzard-65E963A9
kibuzzard-65E963AE: G***; kibuzzard-65E963AE
kibuzzard-65E969A0: G***; kibuzzard-65E969A0
kibuzzard-65E969A4: G***; kibuzzard-65E969A4
kibuzzard-65E969AA: G***; kibuzzard-65E969AA
kibuzzard-65E969AE: G***; kibuzzard-65E969AE
kibuzzard-65E969B1: G***; kibuzzard-65E969B1
kibuzzard-65E969B6: G***; kibuzzard-65E969B6
kibuzzard-65E969BA: G***; kibuzzard-65E969BA
kibuzzard-65E969BF: G***; kibuzzard-65E969BF
kibuzzard-65E969C2: G***; kibuzzard-65E969C2
kibuzzard-65E969C6: G***; kibuzzard-65E969C6
kibuzzard-65E969CA: G***; kibuzzard-65E969CA
kibuzzard-65E969CE: G***; kibuzzard-65E969CE
kibuzzard-65E969D2: G***; kibuzzard-65E969D2
kibuzzard-65E969D5: G***; kibuzzard-65E969D5
kibuzzard-65E969DA: G***; kibuzzard-65E969DA
kibuzzard-65E969DD: G***; kibuzzard-65E969DD
kibuzzard-65E969E1: G***; kibuzzard-65E969E1
kibuzzard-65E969E5: G***; kibuzzard-65E969E5
kibuzzard-65E969E9: G***; kibuzzard-65E969E9
kibuzzard-65E969ED: G***; kibuzzard-65E969ED
kibuzzard-65E9630A: G***; kibuzzard-65E9630A
kibuzzard-65E9633C: G***; kibuzzard-65E9633C
kibuzzard-65E9636C: G***; kibuzzard-65E9636C
kibuzzard-65E9638D: G***; kibuzzard-65E9638D
kibuzzard-65E9639B: G***; kibuzzard-65E9639B
kibuzzard-65E9639F: G***; kibuzzard-65E9639F
kibuzzard-65E9696D: G***; kibuzzard-65E9696D
kibuzzard-65E9697B: G***; kibuzzard-65E9697B
kibuzzard-65E9698D: G***; kibuzzard-65E9698D
kibuzzard-65E9699C: G***; kibuzzard-65E9699C
kibuzzard-65E96100: G***; kibuzzard-65E96100
kibuzzard-65E96303: G***; kibuzzard-65E96303
kibuzzard-65E96310: G***; kibuzzard-65E96310
kibuzzard-65E96314: G***; kibuzzard-65E96314
kibuzzard-65E96318: G***; kibuzzard-65E96318
kibuzzard-65E96322: G***; kibuzzard-65E96322
kibuzzard-65E96383: G***; kibuzzard-65E96383
kibuzzard-65E96396: G***; kibuzzard-65E96396
kibuzzard-65E96959: G***; kibuzzard-65E96959
kibuzzard-65E96962: G***; kibuzzard-65E96962
kibuzzard-65E96967: G***; kibuzzard-65E96967
kibuzzard-65E96973: G***; kibuzzard-65E96973
kibuzzard-65E96977: G***; kibuzzard-65E96977
kibuzzard-65E96980: G***; kibuzzard-65E96980
kibuzzard-65E96984: G***; kibuzzard-65E96984
kibuzzard-65E96989: G***; kibuzzard-65E96989
kibuzzard-65E96991: G***; kibuzzard-65E96991
kibuzzard-65E96995: G***; kibuzzard-65E96995
kibuzzard-65E96999: G***; kibuzzard-65E96999
